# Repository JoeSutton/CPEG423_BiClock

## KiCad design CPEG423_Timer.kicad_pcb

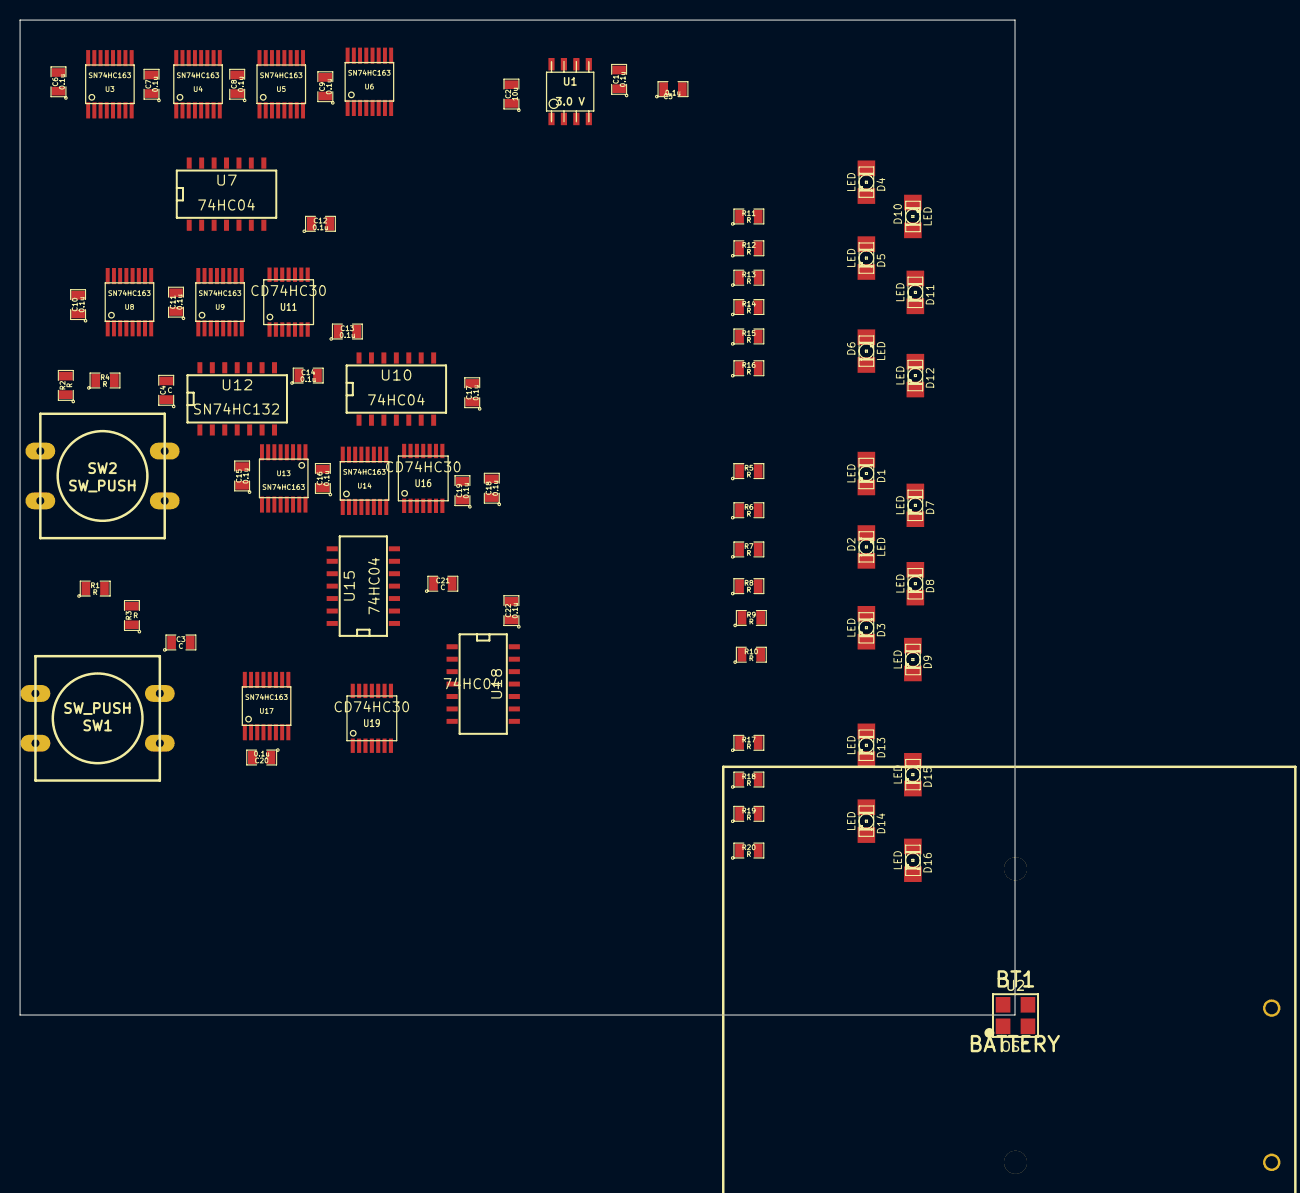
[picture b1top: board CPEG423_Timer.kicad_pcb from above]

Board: 2 copper layers, 101.6 x 101.6 mm, 80 parts (0 on the bottom side), 68 nets, no tracks yet.

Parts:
BT1: BATTERY; BC3AAPC
C1, C5, C6, C7, C8, C9, C10, C11, C12, C13, C14, C15, C16, C17, C18, C19, C20, C22: 0.1u; SM0805
C2: 10u; SM0805
C3, C4, C21: C; SM0805
D1, D2, D3, D4, D5, D6, D7, D8, D9, D10, D11, D12, D13, D14, D15, D16: LED; LED-1206
R1, R2, R3, R4, R5, R6, R7, R8, R9, R10, R11, R12, R13, R14, R15, R16, R17, R18, R19, R20: R; SM0805
SW1, SW2: SW_PUSH; SW_PUSH-12mm
U1: 3.0 V; so-8
U2: OSC; Si501
U3, U4, U5, U6, U8, U9, U13, U14, U17: SN74HC163; ssop-16
U7, U10, U15, U18: 74HC04; SO14N
U11, U16, U19: CD74HC30; tssop-14
U12: SN74HC132; SO14N

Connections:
/hours/Hour_In: U12.6, U17.2
/hours/hours_b<0>: R17.1, U15.10, U19.5
/hours/hours_b<1>: R18.1, U15.8, U19.6
/hours/hours_b<2>: R19.1, U15.6
/hours/hours_b<3>: R20.1, U15.4
/main_counter/Osc_In: U2.3, U3.2, U4.2, U5.2, U6.2
/minutes/Hour_Advance_In: C3.1, R3.2, U12.4
/minutes/Minute_In: U12.3, U13.2, U14.2
/minutes/minutes_b<0>: R5.1, U10.8
/minutes/minutes_b<1>: R6.1, U10.6
/minutes/minutes_b<2>: R7.1, U15.2, U16.11
/minutes/minutes_b<3>: R8.1, U10.4
/minutes/minutes_b<4>: R9.1, U10.10
/minutes/minutes_b<5>: R10.1, U10.12
/seconds/Minute_Advance_In: C4.1, R4.2, U12.1
/seconds/Second_In: U6.11, U7.1, U8.2, U9.2
/seconds/seconds_b<0>: R11.1, U7.8
/seconds/seconds_b<1>: R12.1, U7.6
/seconds/seconds_b<2>: R13.1, U10.2, U11.11
/seconds/seconds_b<3>: R14.1, U7.4
/seconds/seconds_b<4>: R15.1, U7.10
/seconds/seconds_b<5>: R16.1, U7.12
GND: BT1.2, C1.2, C2.2, C3.2, C4.2, C5.1, C6.1, C7.1, C8.1, C9.1, C10.2, C11.1, C12.2, C13.1, C14.1, C15.2, C16.1, C17.2, C18.1, C19.1, C20.2, C21.2, C22.1, SW1.1, SW2.1, U2.2, U3.4, U3.5, U3.6, U4.3, U4.4, U4.5, U4.6, U5.3, U5.4, U5.5, U5.6, U6.3, U6.4, U6.5, U6.6, U7.7, U8.4, U8.5, U8.6, U9.3, U9.4, U9.5, U9.6, U10.7, U12.8, U12.9, U12.10, U12.11, U12.12, U12.13, U13.4, U13.5, U13.6, U14.3, U14.4, U14.5, U14.6, U15.7, U15.12, U15.13, U17.4, U17.5, U17.6, U18.1, U18.2, U18.7
unnamed: R2.2, R4.1, SW2.2
unnamed: D3.2, R9.2
unnamed: D9.2, R10.2
unnamed: D1.2, R5.2
unnamed: R1.2, R3.1, SW1.2
unnamed: D13.2, R17.2
unnamed: D16.2, R20.2
unnamed: D14.2, R19.2
unnamed: D15.2, R18.2
unnamed: BT1.1, C1.1
unnamed: D4.2, R11.2
unnamed: D6.2, R15.2
unnamed: D12.2, R16.2
unnamed: D8.2, R8.2
unnamed: D2.2, R7.2
unnamed: D7.2, R6.2
unnamed: D11.2, R14.2
unnamed: D5.2, R13.2
unnamed: D10.2, R12.2
unnamed: U3.9, U4.1, U5.1, U6.1, U7.2
unnamed: U4.15, U5.10
unnamed: U3.15, U4.10
unnamed: U5.15, U6.10
unnamed: U8.15, U9.10
unnamed: U8.9, U11.8, U12.2
unnamed: U7.3, U8.11, U9.1, U11.12
unnamed: U7.11, U9.14, U11.3
unnamed: U8.12, U10.1
unnamed: U7.5, U8.13, U11.6
unnamed: U7.9, U8.14, U11.5
unnamed: U7.13, U9.13, U11.4
unnamed: U10.11, U14.14, U16.3
unnamed: U10.3, U13.11, U16.12
unnamed: U13.15, U14.10
unnamed: U10.5, U13.13, U16.6
unnamed: U10.9, U13.14, U16.5
unnamed: U12.5, U13.9, U14.1, U16.8
unnamed: U10.13, U14.13, U16.4
unnamed: U13.12, U15.1
unnamed: U15.11, U17.14
unnamed: U15.5, U17.12, U19.11
unnamed: U15.3, U17.11, U19.12
unnamed: U15.9, U17.13
unnamed: U17.9, U19.8
VCC: C2.1, C5.2, C6.2, C7.2, C8.2, C9.2, C10.1, C11.2, C12.1, C13.2, C14.2, C15.1, C16.2, C17.1, C18.2, C19.2, C20.1, C21.1, C22.2, D1.1, D2.1, D3.1, D4.1, D5.1, D6.1, D7.1, D8.1, D9.1, D10.1, D11.1, D12.1, D13.1, D14.1, D15.1, D16.1, R1.1, R2.1, U2.4, U3.1, U3.3, U3.7, U3.10, U4.7, U4.9, U5.7, U5.9, U6.7, U6.9, U7.14, U8.1, U8.3, U8.7, U8.10, U9.7, U9.9, U10.14, U11.1, U11.2, U13.1, U13.3, U13.7, U13.10, U14.7, U14.9, U15.14, U16.1, U16.2, U17.1, U17.3, U17.7, U17.10, U18.14, U19.1, U19.2, U19.3, U19.4

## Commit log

2015-06-26 Revert "Initial commit"
    This reverts commit 1ea9f38c7e70978e3a58808f8fbf7b113b91175d.
2015-06-26 1. Added Project files from Guru
    PCB layout expanded and grouped.
2015-06-26 Completed Netlist & Updated Layout
    Associated OSC with Si501 footprint (.cmp). Reread netlist into layout
    editor (.kicad_pcb) adding battery and oscillator footprints.
